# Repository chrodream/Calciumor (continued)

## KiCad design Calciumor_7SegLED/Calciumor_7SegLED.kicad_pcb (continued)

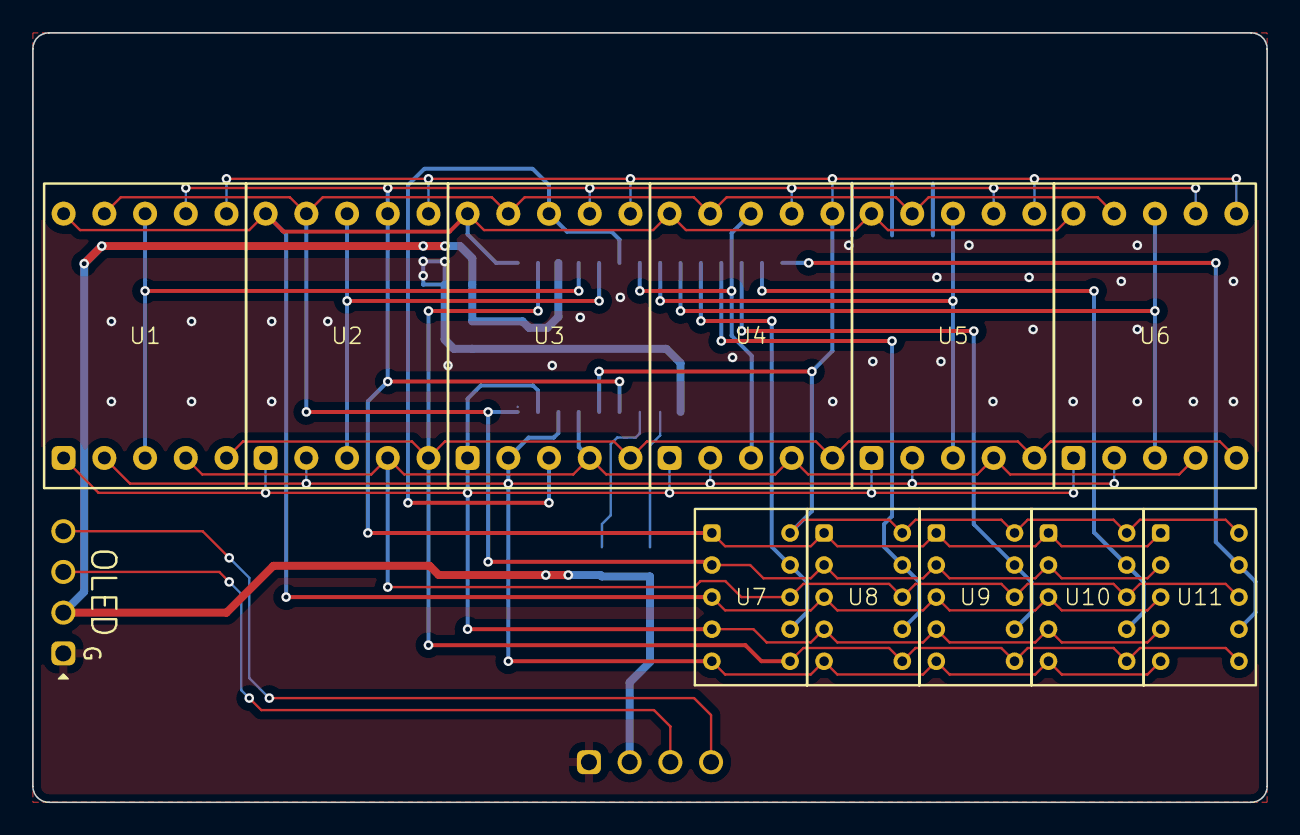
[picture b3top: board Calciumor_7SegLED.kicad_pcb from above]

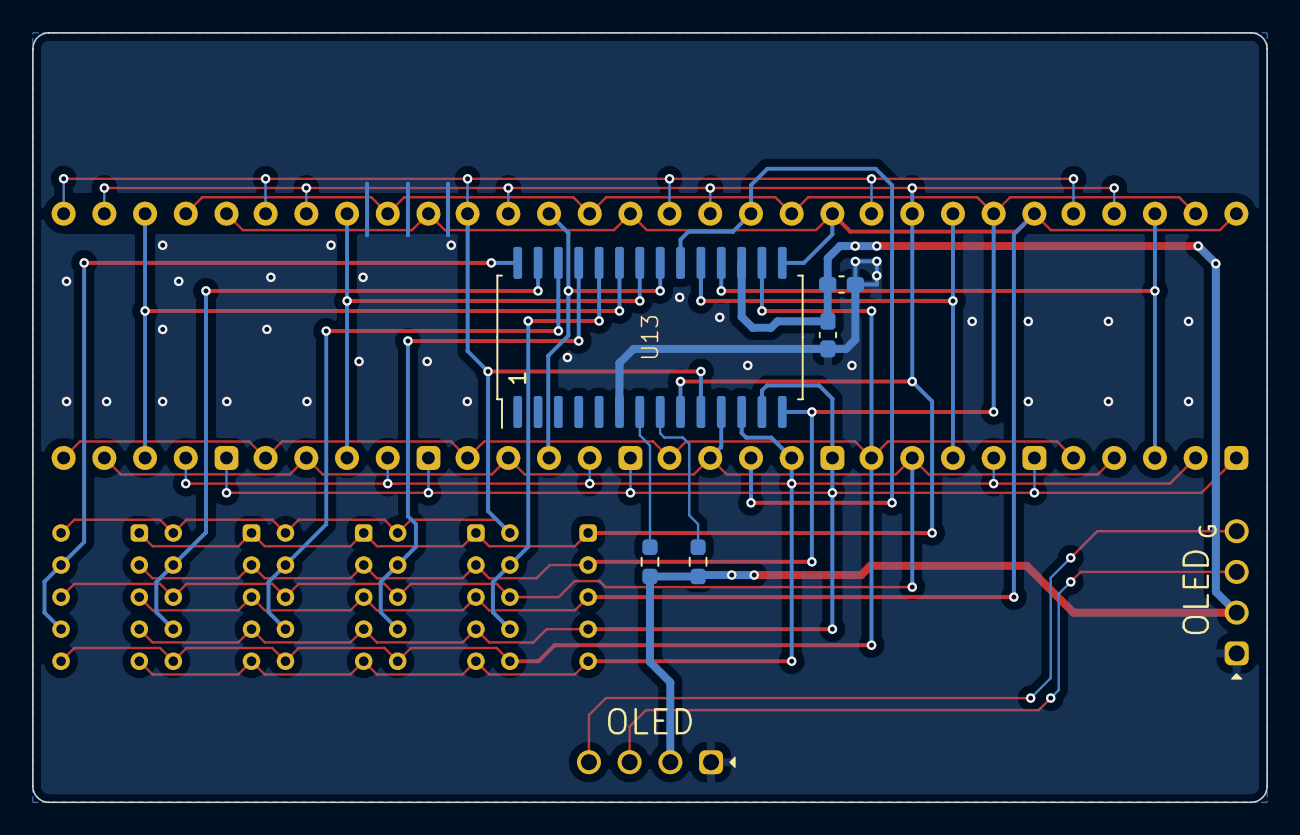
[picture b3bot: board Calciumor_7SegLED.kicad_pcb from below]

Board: 2 copper layers, 77.0 x 48.0 mm, 18 parts (6 on the bottom side), 25 nets.

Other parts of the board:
J1: OLED; I2C
J2: OLED

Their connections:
+5V: J1.3, J2.3; also elsewhere on the board
/SCL: J1.2, J2.2
/SDA: J1.1, J2.1
GND: J1.4, J2.4; also elsewhere on the board

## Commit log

2024-03-23 Changed to socket switch type
2024-03-26 Adjust Patterns and Pastes
2024-03-30 Fixed 2V5 Power supply
2024-04-11 add 5V power source
2024-04-25 Changed to native USB
2024-05-06 Core_rev1.0
2024-05-08 Under cover completed
